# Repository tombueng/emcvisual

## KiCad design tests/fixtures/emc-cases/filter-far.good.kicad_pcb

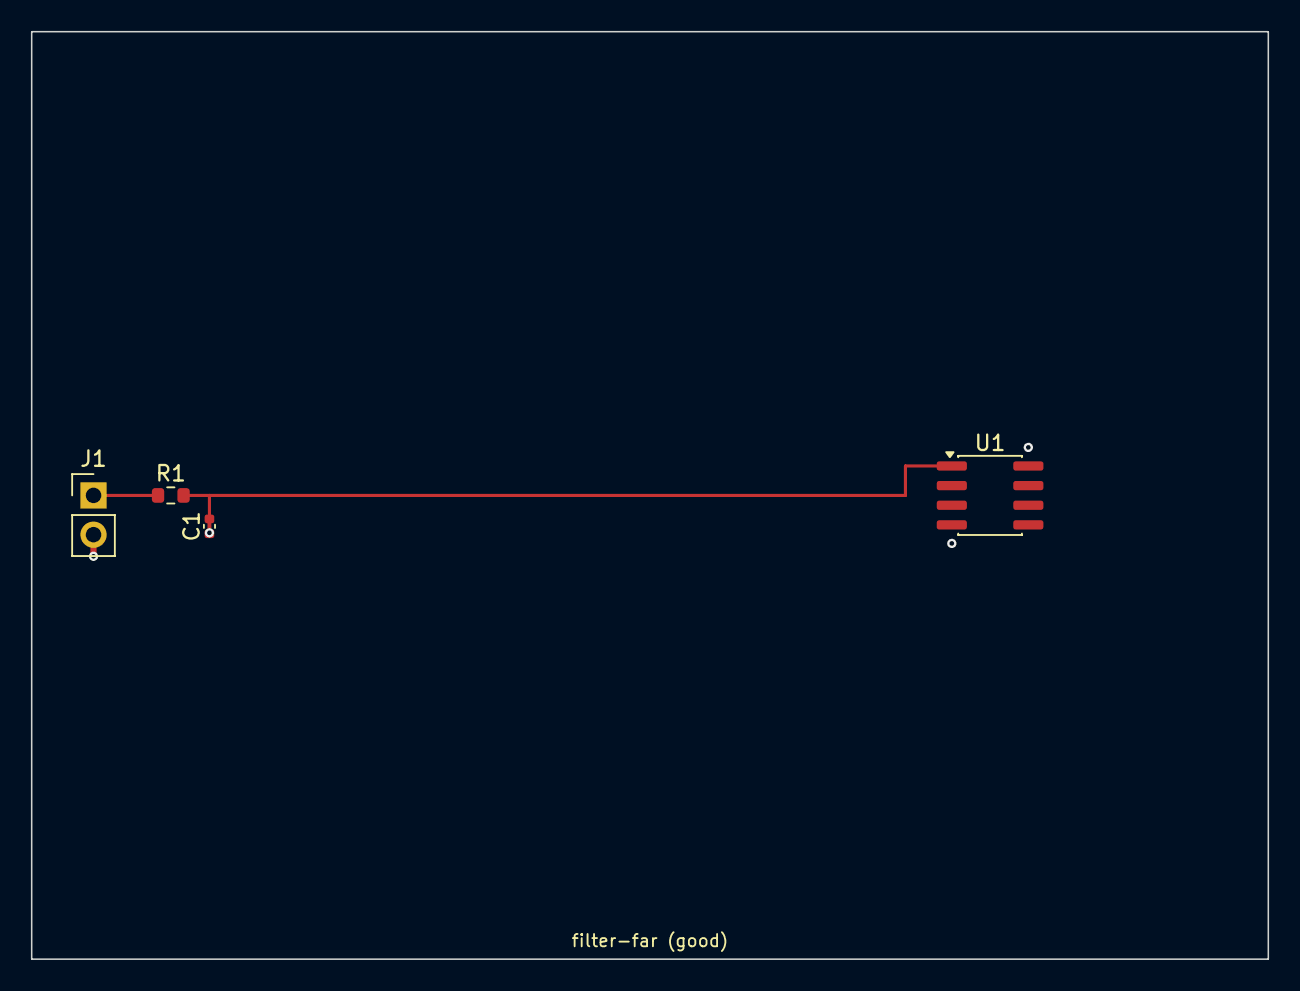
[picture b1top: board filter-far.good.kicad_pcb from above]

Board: 4 copper layers, 80.0 x 60.0 mm, 4 parts (0 on the bottom side), 3 nets.

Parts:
C1: 1nF; C_0402_1005Metric
J1: IO; PinHeader_1x02_P2.54mm_Vertical
R1: 100R; R_0603_1608Metric
U1: MCU; SOIC-8_3.9x4.9mm_P1.27mm

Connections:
GND: C1.2, J1.2, U1.4
IO_IN: J1.1, R1.1
IO_U: C1.1, R1.2, U1.1

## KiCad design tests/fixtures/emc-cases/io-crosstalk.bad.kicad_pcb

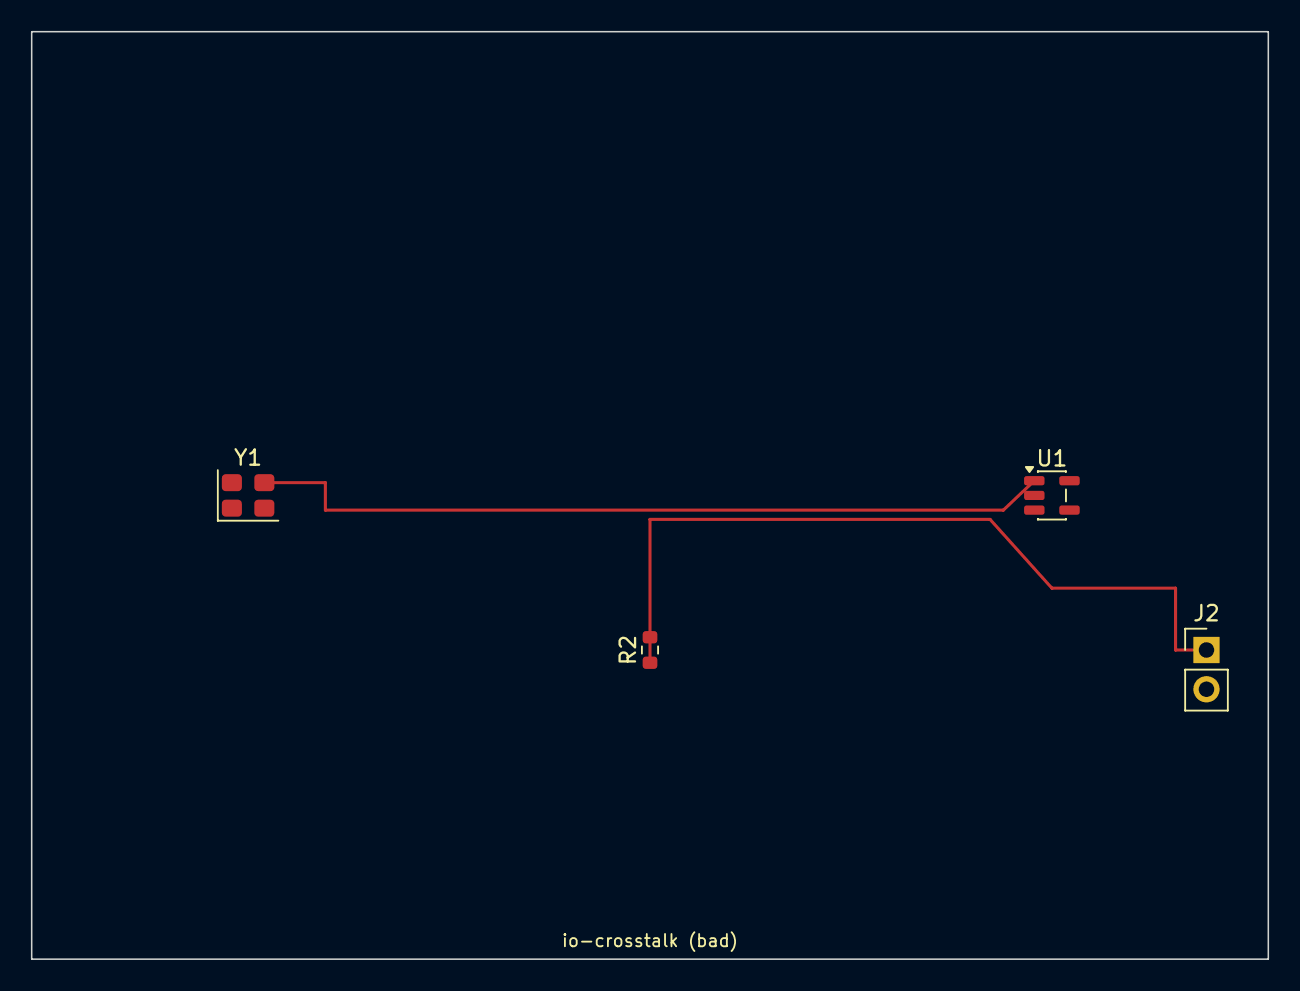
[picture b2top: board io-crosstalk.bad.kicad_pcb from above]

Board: 4 copper layers, 80.0 x 60.0 mm, 4 parts (0 on the bottom side), 4 nets.

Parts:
J2: Taster; PinHeader_1x02_P2.54mm_Vertical
R2: 10k; R_0603_1608Metric
U1: 74LVC1G04; SOT-23-5
Y1: 25MHz; Oscillator_SMD_Abracon_ASE-4Pin_3.2x2.5mm

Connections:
+3V3: R2.2, U1.5, Y1.1, Y1.4
CLK: U1.1, Y1.3
GND: J2.2, U1.2, Y1.2
IO_BTN: J2.1, R2.1
